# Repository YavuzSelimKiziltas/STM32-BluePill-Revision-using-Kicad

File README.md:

# STM32 BluePill Revision using Kicad
 Kicad PCB Files for STM32 BluePill Project 
 
 This PCB is drawn from the **Phil's Lab** youtube channel. Click [here](https://youtu.be/aVUqaB0IMh4) to watch the video: <br/>

 ### Information about PCB:
 PCB dimensions are 42x42 mm. <br/>
 Bottom layer is used as a power plane and connected to the GND to reduce impedance. <br/>
 An SPDT switch is used to manually activate bootloader. <br/>
 120R Ferrite Bead is used to filter high frequency noise around 100MHz. <br/> 
 
 ### Used Materials:
 3 x (1x4) Male Headers <br/>
 1 x STM32F103C8T6 MCU <br/> 
 1 x 16 MHz Crystak Oscillator <br/ 
 1 x AMS1117-3.3 linear voltage regulator <br/>
 1 x Type-B Micro female USB port  <br/>
 4 x 1k5 1206 SMD Resistor  <br/>
 1 x 10k 1206 SMD Resistor <br/>
 2 x 22uF 1206 SMD Capacitor <br/>
 5 x 100nF 1206 SMD Capacitor <br/>
 2 x 10pF 1206 SMD Capacitor <br/>
 2 x 1uF 1206 SMD Capacitor <br/>
 1 x 10nF 1206 SMD Capacitor <br/>
 1 x 0805 RED LED <br/>
 1 x SDPT Button switch <br/>
 1 x 120R Ferrite bead <br/>
 
 ## PCB Board and Schematic Images:
 ### Schematics of the Circuit Diagram:
 
 ### PCB Layout and Routing:
 
 ### Top Layer of the 3D PCB Board:
 
 ### Bottom Layer of the 3D PCB Board:

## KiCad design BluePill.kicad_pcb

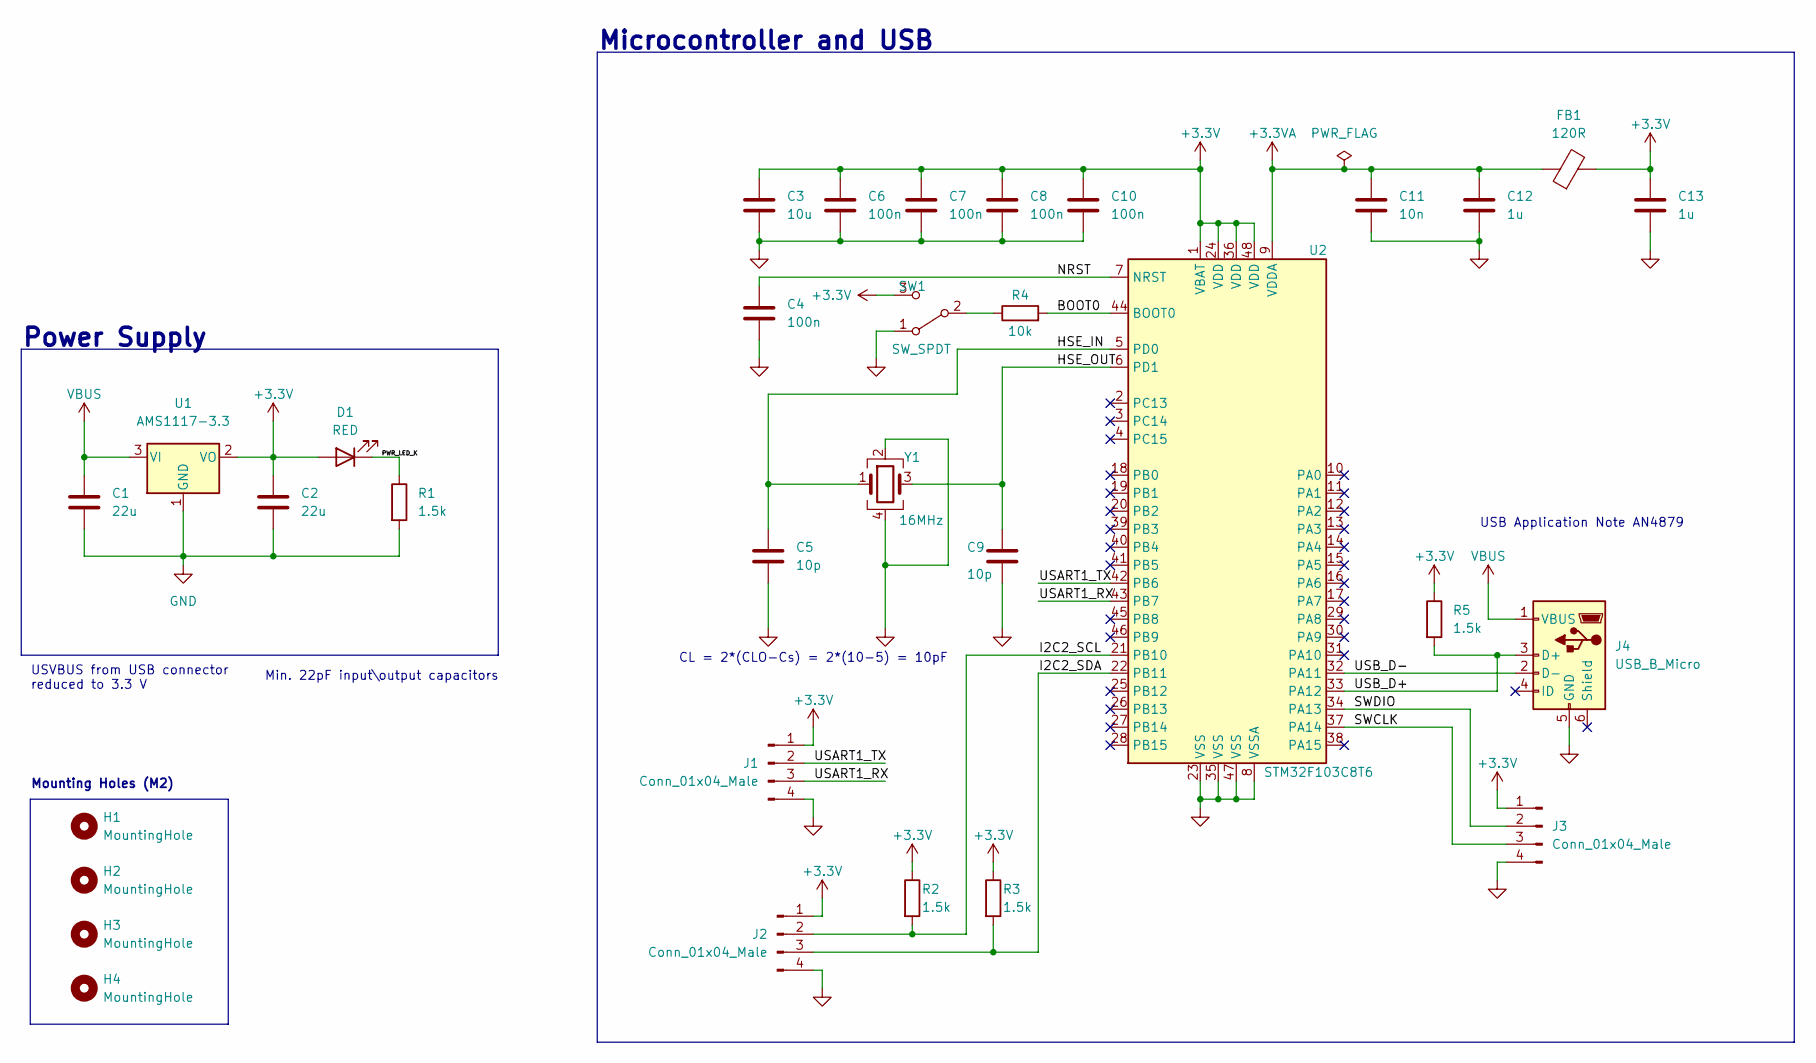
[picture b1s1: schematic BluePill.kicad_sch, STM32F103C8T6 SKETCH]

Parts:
C1, C2: 22u; C_1206_3216Metric_Pad1.33x1.80mm_HandSolder
C3: 10u; C_1206_3216Metric_Pad1.33x1.80mm_HandSolder
C4, C6, C7, C8, C10: 100n; C_1206_3216Metric_Pad1.33x1.80mm_HandSolder
C5, C9: 10p; C_1206_3216Metric_Pad1.33x1.80mm_HandSolder
C11: 10n; C_1206_3216Metric_Pad1.33x1.80mm_HandSolder
C12, C13: 1u; C_1206_3216Metric_Pad1.33x1.80mm_HandSolder
D1: RED; LED_0805_2012Metric_Pad1.15x1.40mm_HandSolder
FB1: 120R; L_0805_2012Metric_Pad1.05x1.20mm_HandSolder
H1, H2, H3, H4: MountingHole; MountingHole_2.2mm_M2
J1, J2, J3: Conn_01x04_Male; PinHeader_1x04_P2.54mm_Vertical
J4: USB_B_Micro; USB_Micro-B_Wuerth_629105150521
R1, R2, R3, R5: 1.5k; R_1206_3216Metric_Pad1.30x1.75mm_HandSolder
R4: 10k; R_1206_3216Metric_Pad1.30x1.75mm_HandSolder
SW1: SW_SPDT; SW_SPDT_PCM12
U1: AMS1117-3.3; SOT-223-3_TabPin2
U2: STM32F103C8T6; LQFP-48_7x7mm_P0.5mm
Y1: 16MHz; Crystal_SMD_3225-4Pin_3.2x2.5mm_HandSoldering

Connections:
+3.3V: C2.1, C3.1, C6.1, C7.1, C8.1, C10.1, C13.1, D1.2 (A), FB1.2, J1.1, J2.1, J3.1, R2.1, R3.1, R5.1, SW1.3 (C), U1.2 (VO), U2.1 (VBAT), U2.24 (VDD), U2.36 (VDD), U2.48 (VDD)
+3.3VA: C11.1, C12.1, FB1.1, U2.9 (VDDA)
/BOOT0: R4.2, U2.44 (BOOT0)
/HSE_IN: C5.1, U2.5 (PD0), Y1.1
/HSE_OUT: C9.1, U2.6 (PD1), Y1.3
/I2C2_SCL: J2.2, R2.2, U2.21 (PB10)
/I2C2_SDA: J2.3, R3.2, U2.22 (PB11)
/NRST: C4.1, U2.7 (NRST)
/PWR_LED_K: D1.1 (K), R1.1
/SWCLK: J3.3, U2.37 (PA14)
/SWDIO: J3.2, U2.34 (PA13)
/USART1_RX: J1.3, U2.43 (PB7)
/USART1_TX: J1.2, U2.42 (PB6)
/USB_D+: J4.3 (D+), R5.2, U2.33 (PA12)
/USB_D-: J4.2 (D-), U2.32 (PA11)
GND: C1.2, C2.2, C3.2, C4.2, C5.2, C6.2, C7.2, C8.2, C9.2, C10.2, C11.2, C12.2, C13.2, J1.4, J2.4, J3.4, J4.5 (GND), R1.2, SW1.1 (A), U1.1 (GND), U2.8 (VSSA), U2.23 (VSS), U2.35 (VSS), U2.47 (VSS), Y1.2, Y1.4
unnamed: R4.1, SW1.2 (B)
VBUS: C1.1, J4.1 (VBUS), U1.3 (VI)

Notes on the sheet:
Microcontroller and USB
USVBUS from USB connector reduced to 3.3 V
CL = 2*(CLO-Cs) = 2*(10-5) = 10pF
Mounting Holes (M2)
Power Supply
Min. 22pF input\output capacitors
USB Application Note AN4879

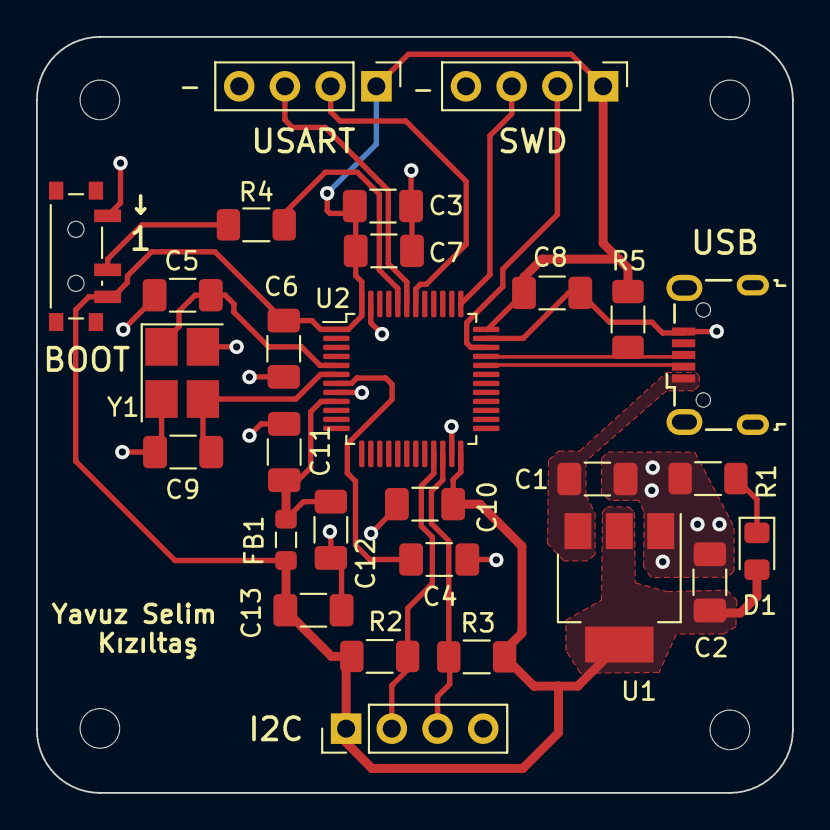
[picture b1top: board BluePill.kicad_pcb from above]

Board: 2 copper layers, 42.0 x 42.0 mm, 32 parts (0 on the bottom side), 18 nets.

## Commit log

2023-02-17 BluePill Revision
